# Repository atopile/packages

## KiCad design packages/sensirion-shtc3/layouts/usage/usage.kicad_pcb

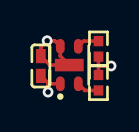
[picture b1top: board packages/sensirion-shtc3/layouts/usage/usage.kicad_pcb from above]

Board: 2 copper layers, 4 parts (0 on the bottom side), 4 nets.

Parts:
C1: 100nF ±10% 16V X7R; C0402
R1, R2: 10kΩ ±1% 62.5mW; R0402
U1: SENSORM-SMD_4P-L2.0-W2.0-P1.00

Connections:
SCL: R1.1, U1.2
SDA: R2.1, U1.3
gnd: C1.2, U1.4, U1.5
hv: C1.1, R1.2, R2.2, U1.1

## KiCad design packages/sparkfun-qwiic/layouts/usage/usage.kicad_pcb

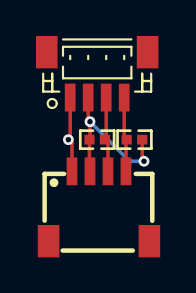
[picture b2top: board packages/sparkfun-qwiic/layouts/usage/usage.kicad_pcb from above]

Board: 2 copper layers, 4 parts (0 on the bottom side), 4 nets.

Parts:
CN1: CONN-SMD_4P-P1.00_SM04B-SRSS-TB-LF-SN
CN2: CONN-SMD_BM04B-SRSS-TB
R1, R2: 10kΩ; R0402

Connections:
SCL: CN1.4, CN2.4, R1.1
SDA: CN1.3, CN2.3, R2.1
hv: CN1.2, CN2.2, R1.2, R2.2
lv: CN1.1, CN1.5, CN1.6, CN2.0, CN2.1

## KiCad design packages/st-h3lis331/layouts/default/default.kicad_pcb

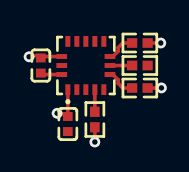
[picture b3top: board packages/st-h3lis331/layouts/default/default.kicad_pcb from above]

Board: 2 copper layers, 7 parts (0 on the bottom side), 7 nets.

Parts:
C1, C2: 100nF; C0402
R1, R2: 10kΩ; R0402
R3, R4: 4.7kΩ; R0402
U1: LGA-16_L3.0-W3.0-P0.50-BL

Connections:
7: R2.2, U1.7
CS: R1.2, U1.8
Reserved: U1.10, U1.15
SCL: R3.1, U1.4
SDA: R4.1, U1.6
hv: C1.1, C2.1, R1.1, R3.2, R4.2, U1.1, U1.14
lv: C1.2, C2.2, R2.1, U1.5, U1.12, U1.13, U1.16

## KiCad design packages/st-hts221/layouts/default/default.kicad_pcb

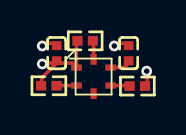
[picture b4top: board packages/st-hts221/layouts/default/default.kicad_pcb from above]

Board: 2 copper layers, 6 parts (0 on the bottom side), 5 nets.

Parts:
C1: 100nF; C0402
C2: 10µF; C0402
R1, R2, R3: 10kΩ; R0402
U1: HLGA-6L_L2.0-M2.0-P1.00-TL

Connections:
CS: R1.2, U1.6
SCL: R2.1, U1.2
SDA: R3.1, U1.4
hv: C1.1, C2.1, R1.1, R2.2, R3.2, U1.1
lv: C1.2, C2.2, U1.5
